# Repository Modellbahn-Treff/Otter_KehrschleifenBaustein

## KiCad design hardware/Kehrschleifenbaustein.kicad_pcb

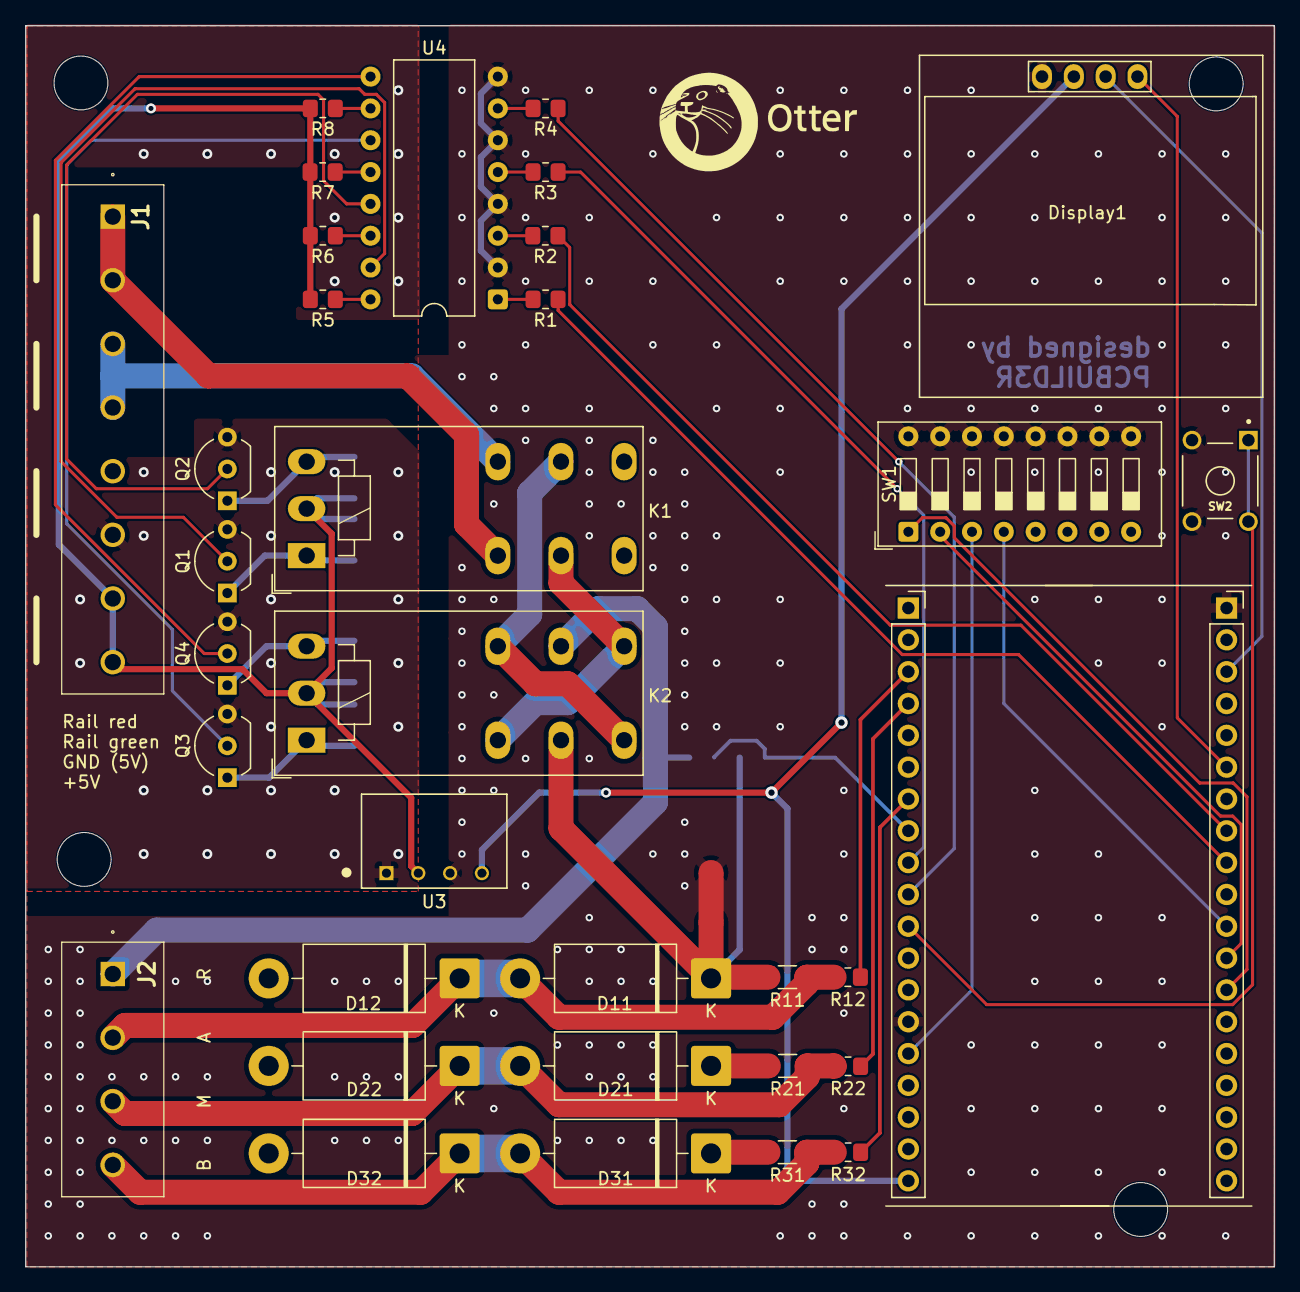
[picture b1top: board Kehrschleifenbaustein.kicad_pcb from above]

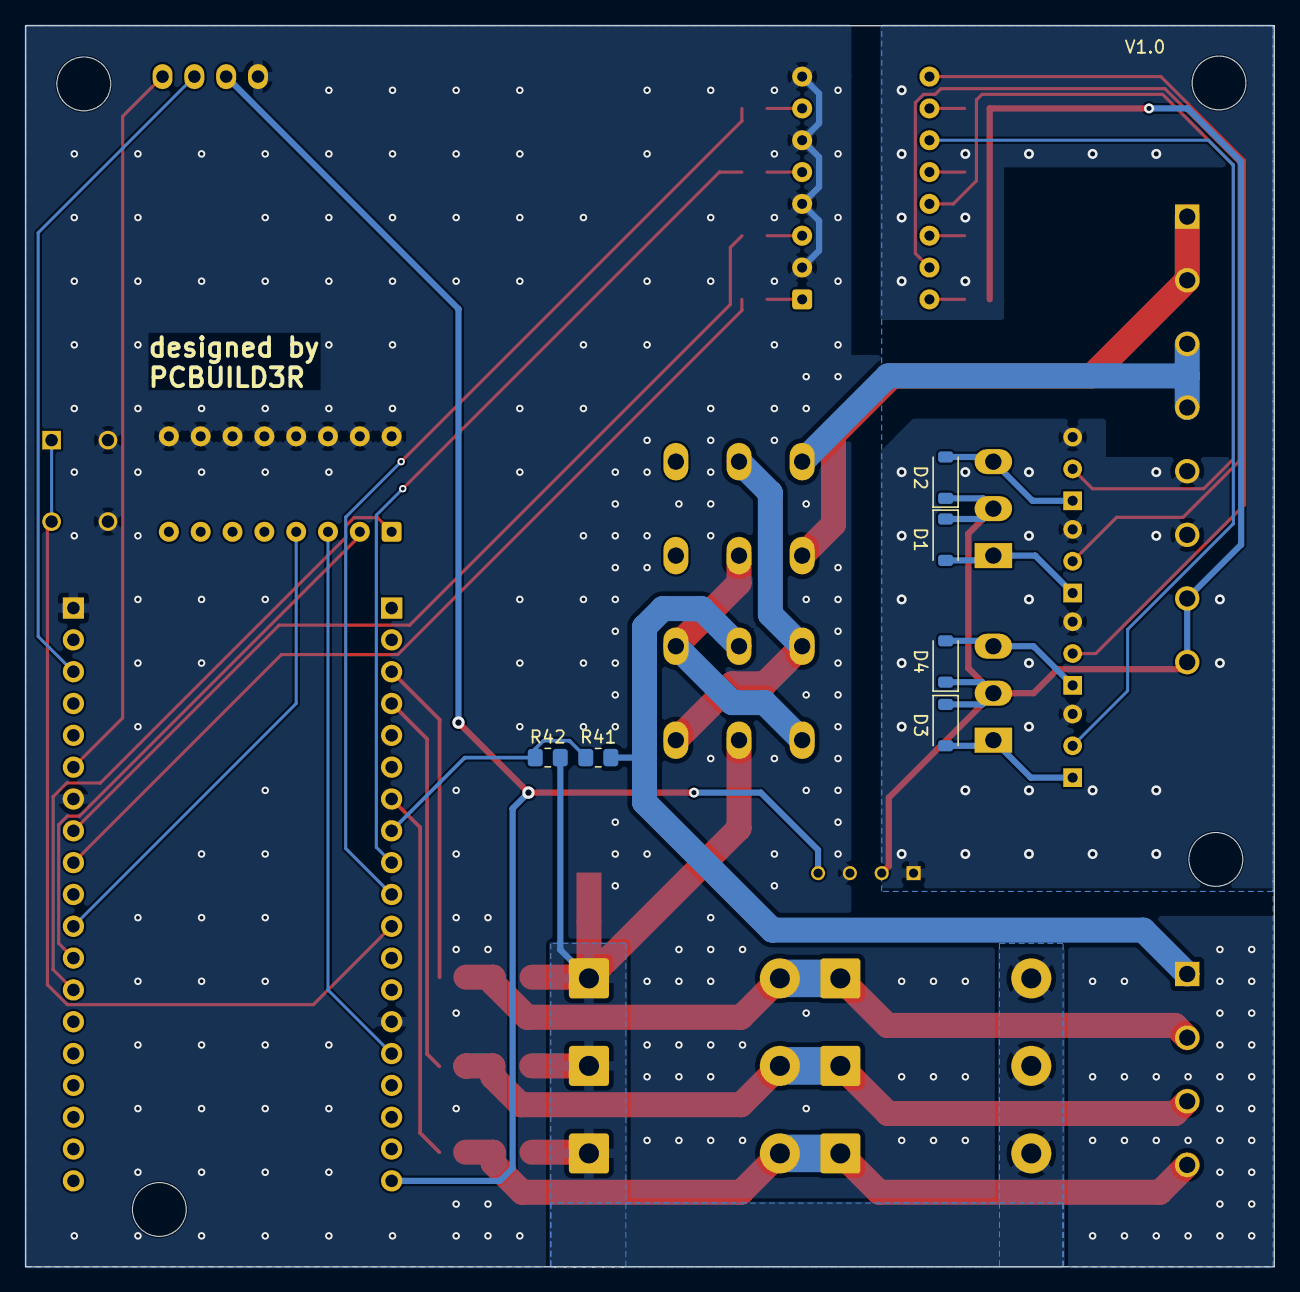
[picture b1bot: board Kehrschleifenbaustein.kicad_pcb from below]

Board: 2 copper layers, 99.7 x 99.1 mm, 46 parts (6 on the bottom side), 44 nets.

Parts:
D1, D2, D3, D4: 1N4148W; D_SOD-123
D11, D12, D21, D22, D31, D32: 1N5402; D_DO-201AD_P15.24mm_Horizontal
Display1: SSD1306; 128x64OLED
H1, H2, H3, H4: MountingHole; MountingHole_4.3mm_M4
J1: Conn_01x08; 1729186
J2: Conn_01x04; 1729144
K1, K2: RT42xFxx; Relay_DPDT_Schrack-RT2-FormC-Dual-Coil_RM5mm
NT1: NetTie_2; NetTie-2_SMD_Pad2.0mm
Q1, Q2, Q3, Q4: BC337; TO-92_Inline_Wide
R1, R2, R3, R4: 330; R_0805_2012Metric_Pad1.20x1.40mm_HandSolder
R5, R6, R7, R8: 1k; R_0805_2012Metric_Pad1.20x1.40mm_HandSolder
R11, R21, R31: 22; R_1206_3216Metric_Pad1.30x1.75mm_HandSolder
R12, R22, R32, R42: 10k; R_0805_2012Metric_Pad1.20x1.40mm_HandSolder
R41: 75k; R_0805_2012Metric_Pad1.20x1.40mm_HandSolder
SW1: SW_DIP_x08; SW_DIP_SPSTx08_Slide_9.78x22.5mm_W7.62mm_P2.54mm
SW2: 1-1825910-4; TE_1-1825910-4
U1: esp32_dev4_right
U2: esp32_dev4_left; esp32_dev_left
U3: SMU02L-05; SIP750W50P254L1160H1014Q4
U4: LTV-847M; DIP-16_W10.16mm

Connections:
5V0-isoliert: Display1.2 (VCC), U2.19 (5V), U3.4 (+VOUT)
+5V: D1.1 (K), D2.1 (K), D3.1 (K), D4.1 (K), J1.7, J1.8, K1.A3, K2.A3, R5.1, R6.1, R7.1, R8.1, U3.2 (+VIN)
+15V: J1.3, J1.4, K1.22
-15V: J1.1, J1.2, K1.12
ADC1_0: R12.2, U2.3 (GPI36)
ADC1_3: R22.2, U2.4 (GPI39)
ADC1_4: R32.2, U2.7 (GPIO32)
ADC1_5: R41.1, R42.2, U2.8 (GPIO33)
BTN_GPIO: SW2.1, SW2.2, U2.11 (GPIO27)
DIP_GPIO1: SW1.1, U1.26 (GPIO4)
DIP_GPIO2: SW1.3, U2.15 (GPIO13)
DIP_GPIO3: SW1.2, U1.27 (GPIO16)
DIP_GPIO4: SW1.4, U1.28 (GPIO17)
GND: J1.5, J1.6, Q1.3 (E), Q2.3 (E), Q3.3 (E), Q4.3 (E), U3.1 (-VIN)
GND-isoliert: Display1.1 (GND), NT1.2, SW1.9, SW1.10, SW1.11, SW1.12, SW1.13, SW1.14, SW1.15, SW1.16, SW2.3, SW2.4, U1.32 (GND), U1.38 (GND), U2.14 (GND), U3.3 (-VOUT), U4.2, U4.4, U4.6, U4.8
IN_A: D11.2 (A), D12.1 (K), J2.2, R11.1, R12.1
IN_B: D31.2 (A), D32.1 (K), J2.4, R31.1, R32.1
IN_M: D21.2 (A), D22.1 (K), J2.3, R21.1, R22.1
unnamed: D1.2 (A), K1.A1, Q1.1 (C)
unnamed: D2.2 (A), K1.A2, Q2.1 (C)
unnamed: D3.2 (A), K2.A1, Q3.1 (C)
unnamed: D4.2 (A), K2.A2, Q4.1 (C)
unnamed: Display1.3 (SCL), U1.36 (GPIO22)
unnamed: Display1.4 (SDA), U1.33 (GPIO21)
unnamed: K1.11, K2.12, K2.24
unnamed: K1.21, K2.14, K2.22
unnamed: Q1.2 (B), U4.15
unnamed: Q2.2 (B), U4.13
unnamed: Q3.2 (B), U4.11
unnamed: Q4.2 (B), U4.9
unnamed: R1.2, U4.1
unnamed: R2.2, U4.3
unnamed: R3.2, U4.5
unnamed: R4.2, U4.7
unnamed: R5.2, U4.16
unnamed: R6.2, U4.14
unnamed: R7.2, U4.12
unnamed: R8.2, U4.10
Rail_inner: J2.1, K2.21, R41.2
Rail_outer: D11.1 (K), D12.2 (A), D21.1 (K), D22.2 (A), D31.1 (K), D32.2 (A), K2.11, NT1.1, R11.2, R21.2, R31.2, R42.1
Relais_GPIO1: R1.1, U1.30 (GPIO18)
Relais_GPIO2: R2.1, U1.31 (GPIO19)
Relais_GPIO3: R3.1, U2.9 (GPIO25)
Relais_GPIO4: R4.1, U2.10 (GPIO26)

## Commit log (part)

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2026-06-07 update DRC
